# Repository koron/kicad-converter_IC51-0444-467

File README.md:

# PCB converts IC51-0444-467 connector to standard pin headers.

This project is schematic of PCB that convert IC51-0444-467's 1.6mm pitch
connector to 2.54mm pitch pin headers.

IC51-0444-467 is QFP44 socket, is available at <https://www.aitendo.com/product/17079>.

There are gerber files in [gerver/r1-jlcpcb-r1](gerver/r1-jlcpcb-r1) directory. So you can order to
produce PCB to [JLCPCB](https://jlcpcb.com/) or similar manufacturers.

NOTE: I just ordered, so not verified to work physically yet.

## Rendered Images

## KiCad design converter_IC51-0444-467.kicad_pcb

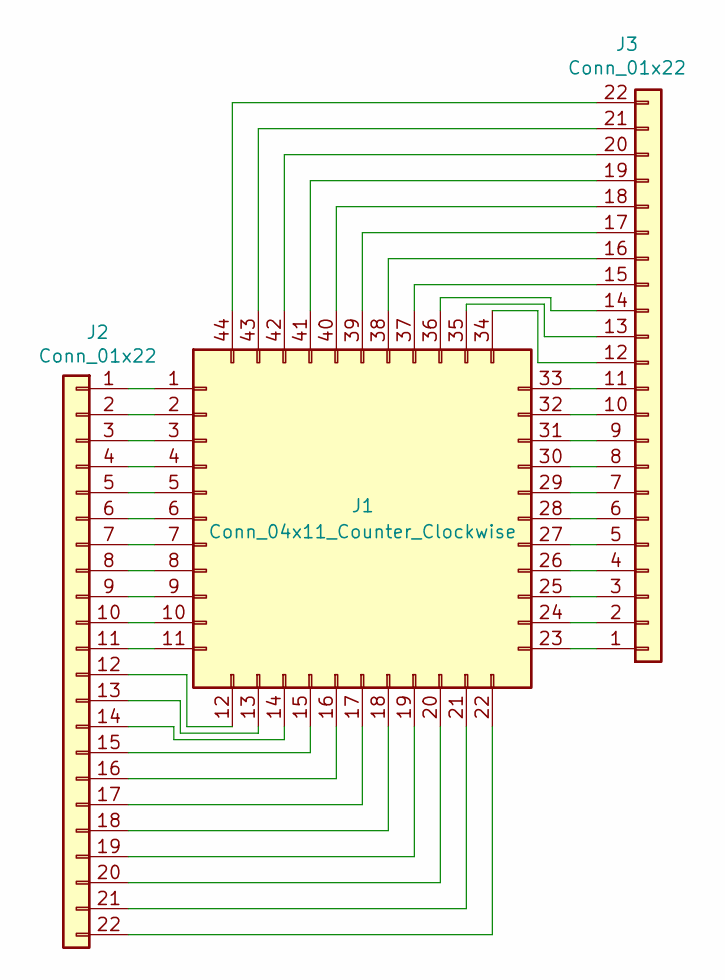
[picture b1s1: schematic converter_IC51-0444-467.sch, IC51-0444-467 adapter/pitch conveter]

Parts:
J1: Conn_04x11_Counter_Clockwise; IC51-0444-467
J2: Conn_01x22; PinHeader_1x22_01-22
J3: Conn_01x22; PinHeader_1x22_23-44

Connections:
unnamed: J1.1, J2.1
unnamed: J1.2, J2.2
unnamed: J1.3, J2.3
unnamed: J1.4, J2.4
unnamed: J1.5, J2.5
unnamed: J1.6, J2.6
unnamed: J1.7, J2.7
unnamed: J1.8, J2.8
unnamed: J1.9, J2.9
unnamed: J1.10, J2.10
unnamed: J1.11, J2.11
unnamed: J1.12, J2.12
unnamed: J1.13, J2.13
unnamed: J1.14, J2.14
unnamed: J1.15, J2.15
unnamed: J1.16, J2.16
unnamed: J1.17, J2.17
unnamed: J1.18, J2.18
unnamed: J1.19, J2.19
unnamed: J1.20, J2.20
unnamed: J1.21, J2.21
unnamed: J1.22, J2.22
unnamed: J1.23, J3.1
unnamed: J1.24, J3.2
unnamed: J1.25, J3.3
unnamed: J1.26, J3.4
unnamed: J1.27, J3.5
unnamed: J1.28, J3.6
unnamed: J1.29, J3.7
unnamed: J1.30, J3.8
unnamed: J1.31, J3.9
unnamed: J1.32, J3.10
unnamed: J1.33, J3.11
unnamed: J1.34, J3.12
unnamed: J1.35, J3.13
unnamed: J1.36, J3.14
unnamed: J1.37, J3.15
unnamed: J1.38, J3.16
unnamed: J1.39, J3.17
unnamed: J1.40, J3.18
unnamed: J1.41, J3.19
unnamed: J1.42, J3.20
unnamed: J1.43, J3.21
unnamed: J1.44, J3.22

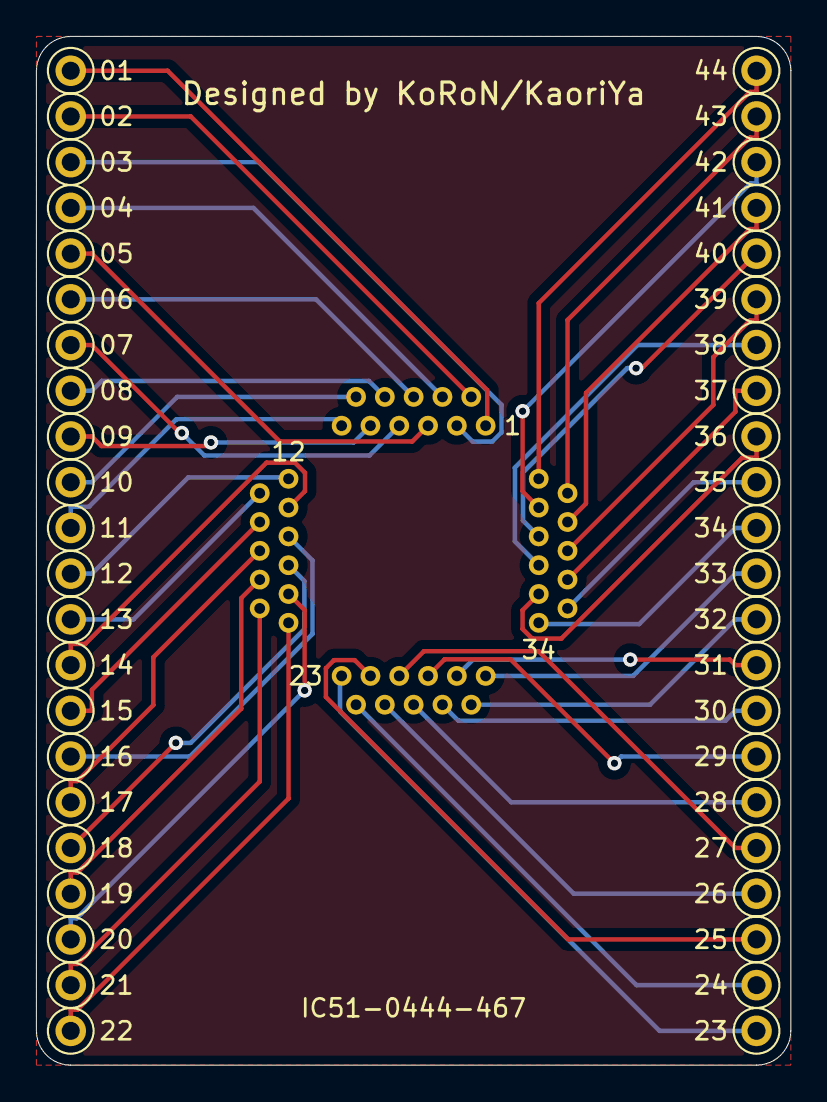
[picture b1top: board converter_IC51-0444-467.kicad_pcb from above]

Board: 2 copper layers, 41.9 x 57.1 mm, 3 parts (0 on the bottom side), 44 nets.

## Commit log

2021-03-20 rev1 finished
2021-03-20 fix link
2021-03-20 add images
